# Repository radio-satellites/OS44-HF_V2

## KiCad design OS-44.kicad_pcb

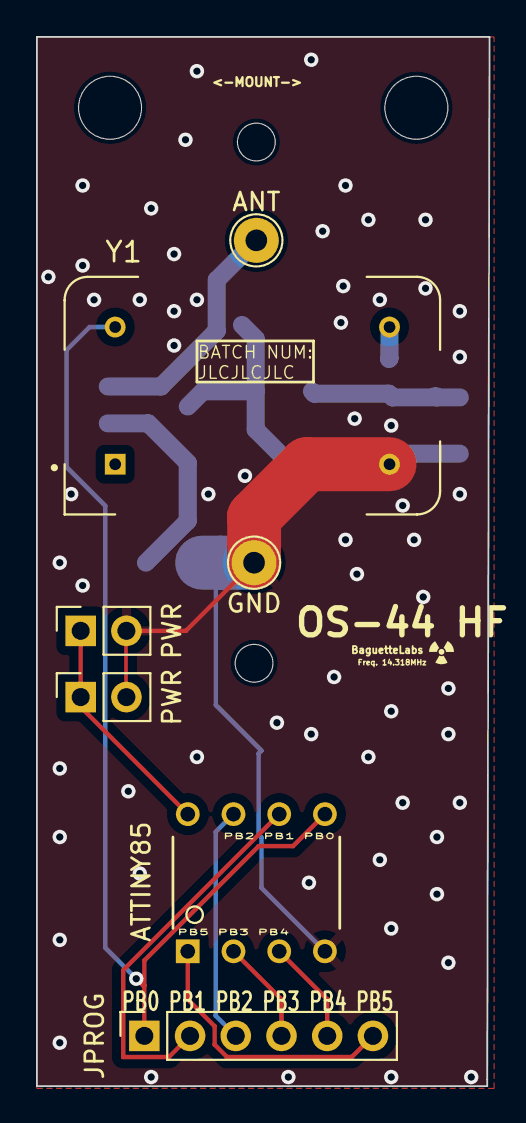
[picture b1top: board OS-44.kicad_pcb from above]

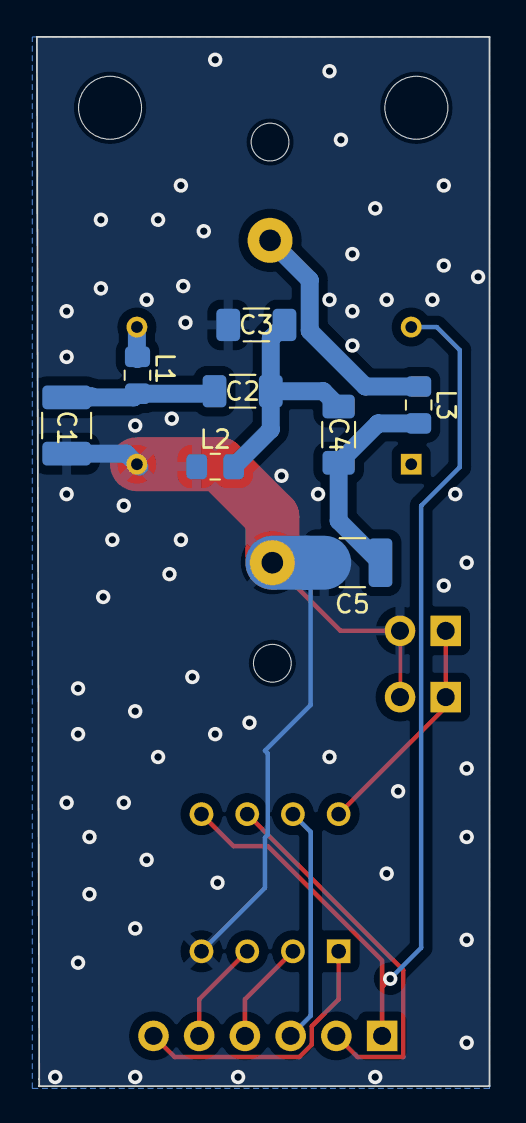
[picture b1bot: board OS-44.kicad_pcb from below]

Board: 2 copper layers, 25.1 x 58.3 mm, 15 parts (8 on the bottom side), 13 nets.

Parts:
ANT: ANT; TestPoint_THTPad_D2.5mm_Drill1.2mm
ATTINY85: ATTINY85-20PU; ATTINY85
C1: C; C_1210_3225Metric_Pad1.33x2.70mm_HandSolder
C2, C4: 18pF; C_1206_3216Metric_Pad1.33x1.80mm_HandSolder
C3: 47pF; C_1206_3216Metric_Pad1.33x1.80mm_HandSolder
C5: 56pF; C_1210_3225Metric_Pad1.33x2.70mm_HandSolder
J4: GND; TestPoint_THTPad_D2.5mm_Drill1.2mm
JPROG: PROG; PinSocket_1x06_P2.54mm_Vertical
L1, L2, L3: 1.5uH; L_0805_2012Metric_Pad1.15x1.40mm_HandSolder
PWR: PWR; PinSocket_1x02_P2.54mm_Vertical
PWR#2: PWR; PinSocket_1x02_P2.54mm_Vertical
Y1: ECS-100A-143; OSC_ECS-100A-143

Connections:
GND: ATTINY85.4 (GND), C1.2, C3.2, C5.2, J4.1, L2.2, PWR.2, Y1.7 (CASE_GND)
HF_MOD: L1.1, Y1.8 (OUTPUT)
unnamed: C1.1, C2.1, L1.2
unnamed: C2.2, C3.1, C4.1, L2.1
unnamed: C4.2, C5.1, L3.1
PB0: ATTINY85.5 (PB0), JPROG.1, Y1.14 (+VDC)
PB1: ATTINY85.6 (PB1), JPROG.2
PB2: ATTINY85.7 (PB2), JPROG.3
PB3: ATTINY85.2 (PB3), JPROG.4
PB4: ATTINY85.3 (PB4), JPROG.5
PB5: ATTINY85.1 (PB5), JPROG.6
RF_OUT: ANT.1, L3.2
VCC: ATTINY85.8 (VCC), PWR.1
